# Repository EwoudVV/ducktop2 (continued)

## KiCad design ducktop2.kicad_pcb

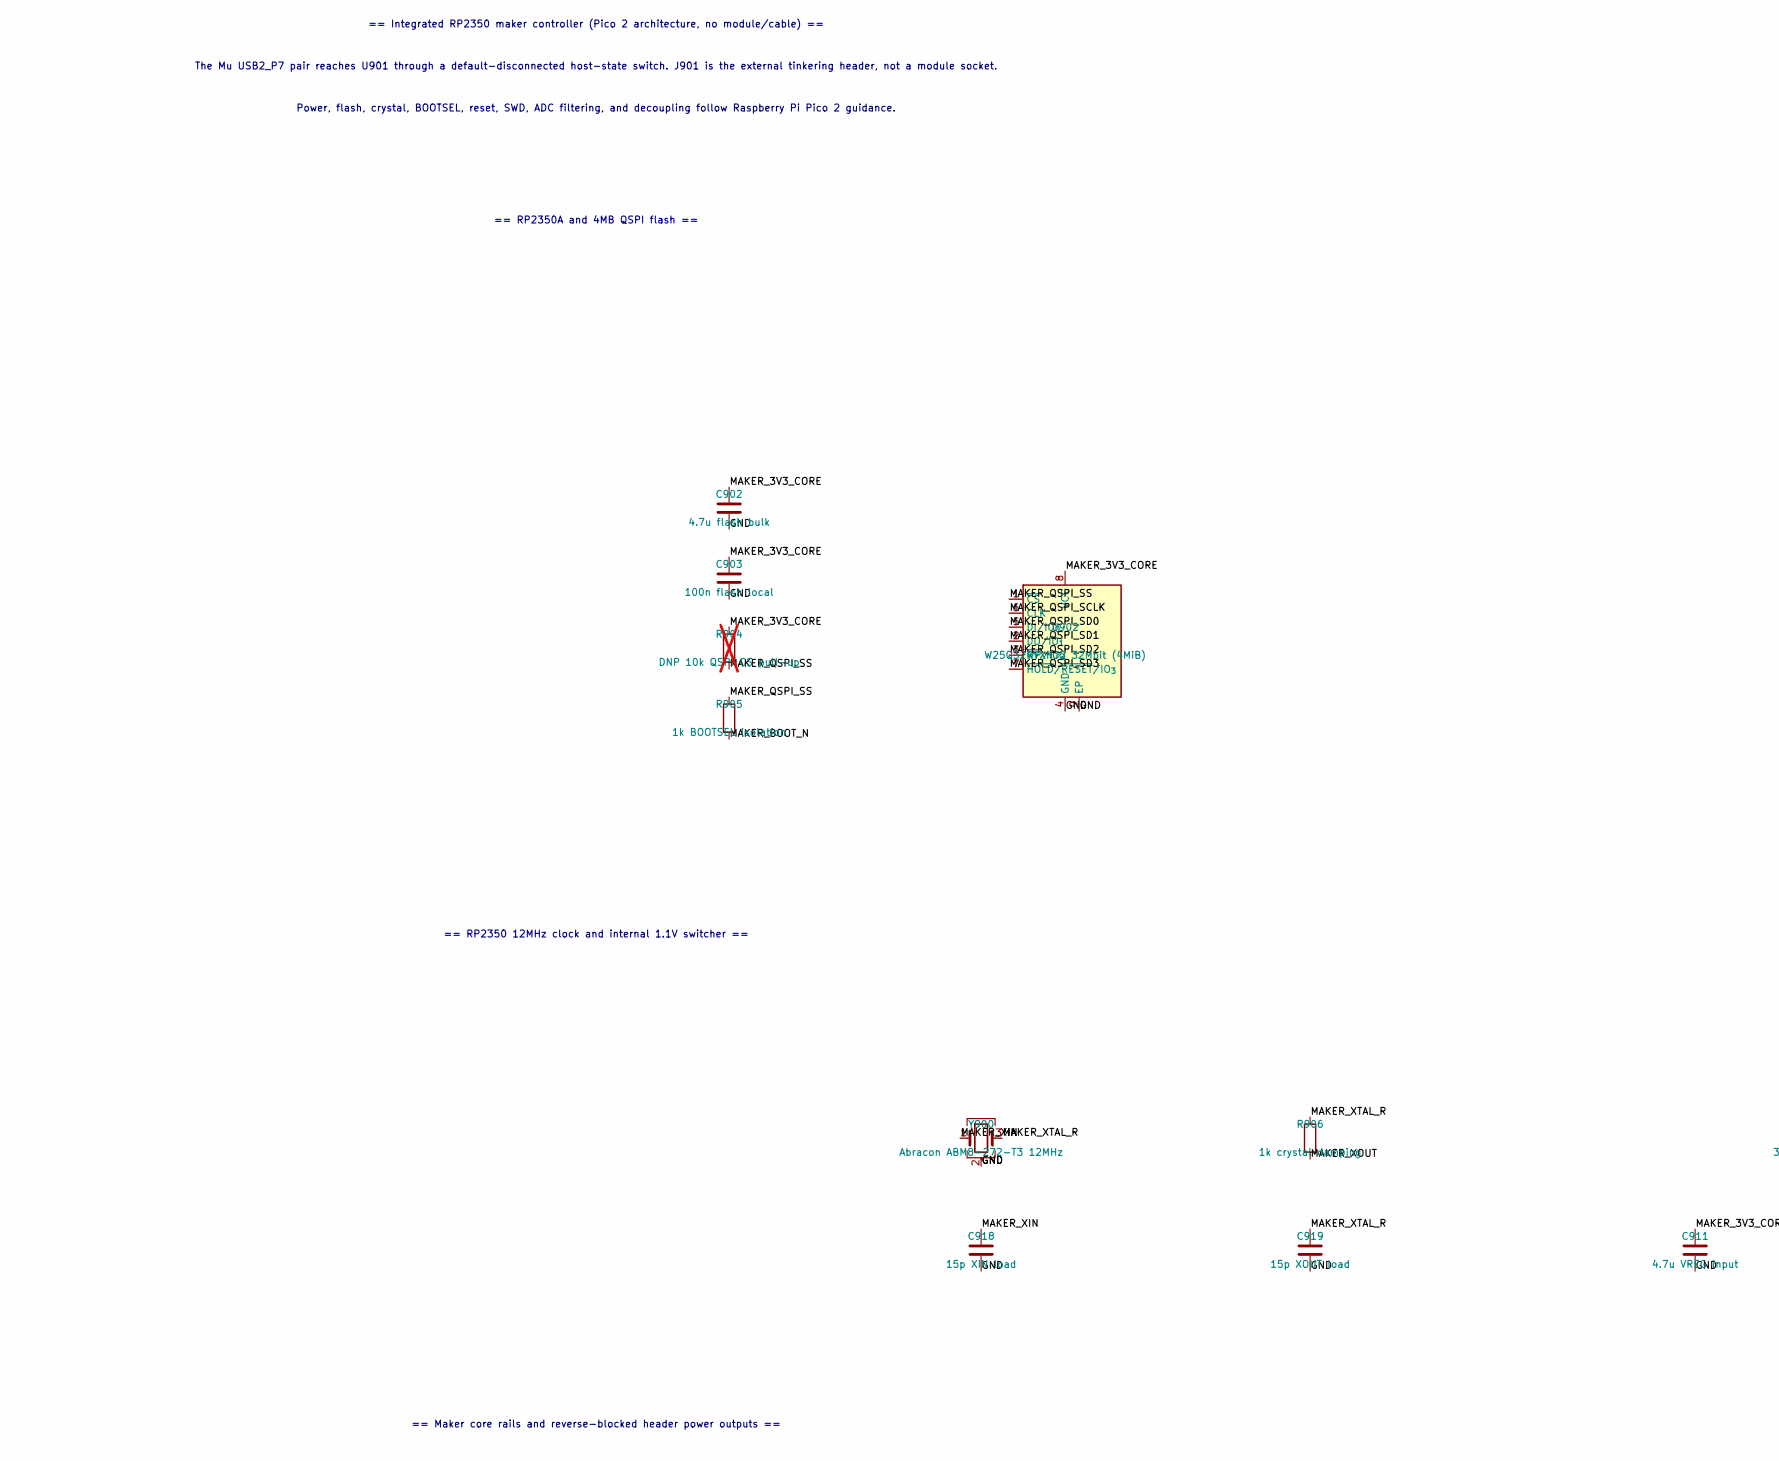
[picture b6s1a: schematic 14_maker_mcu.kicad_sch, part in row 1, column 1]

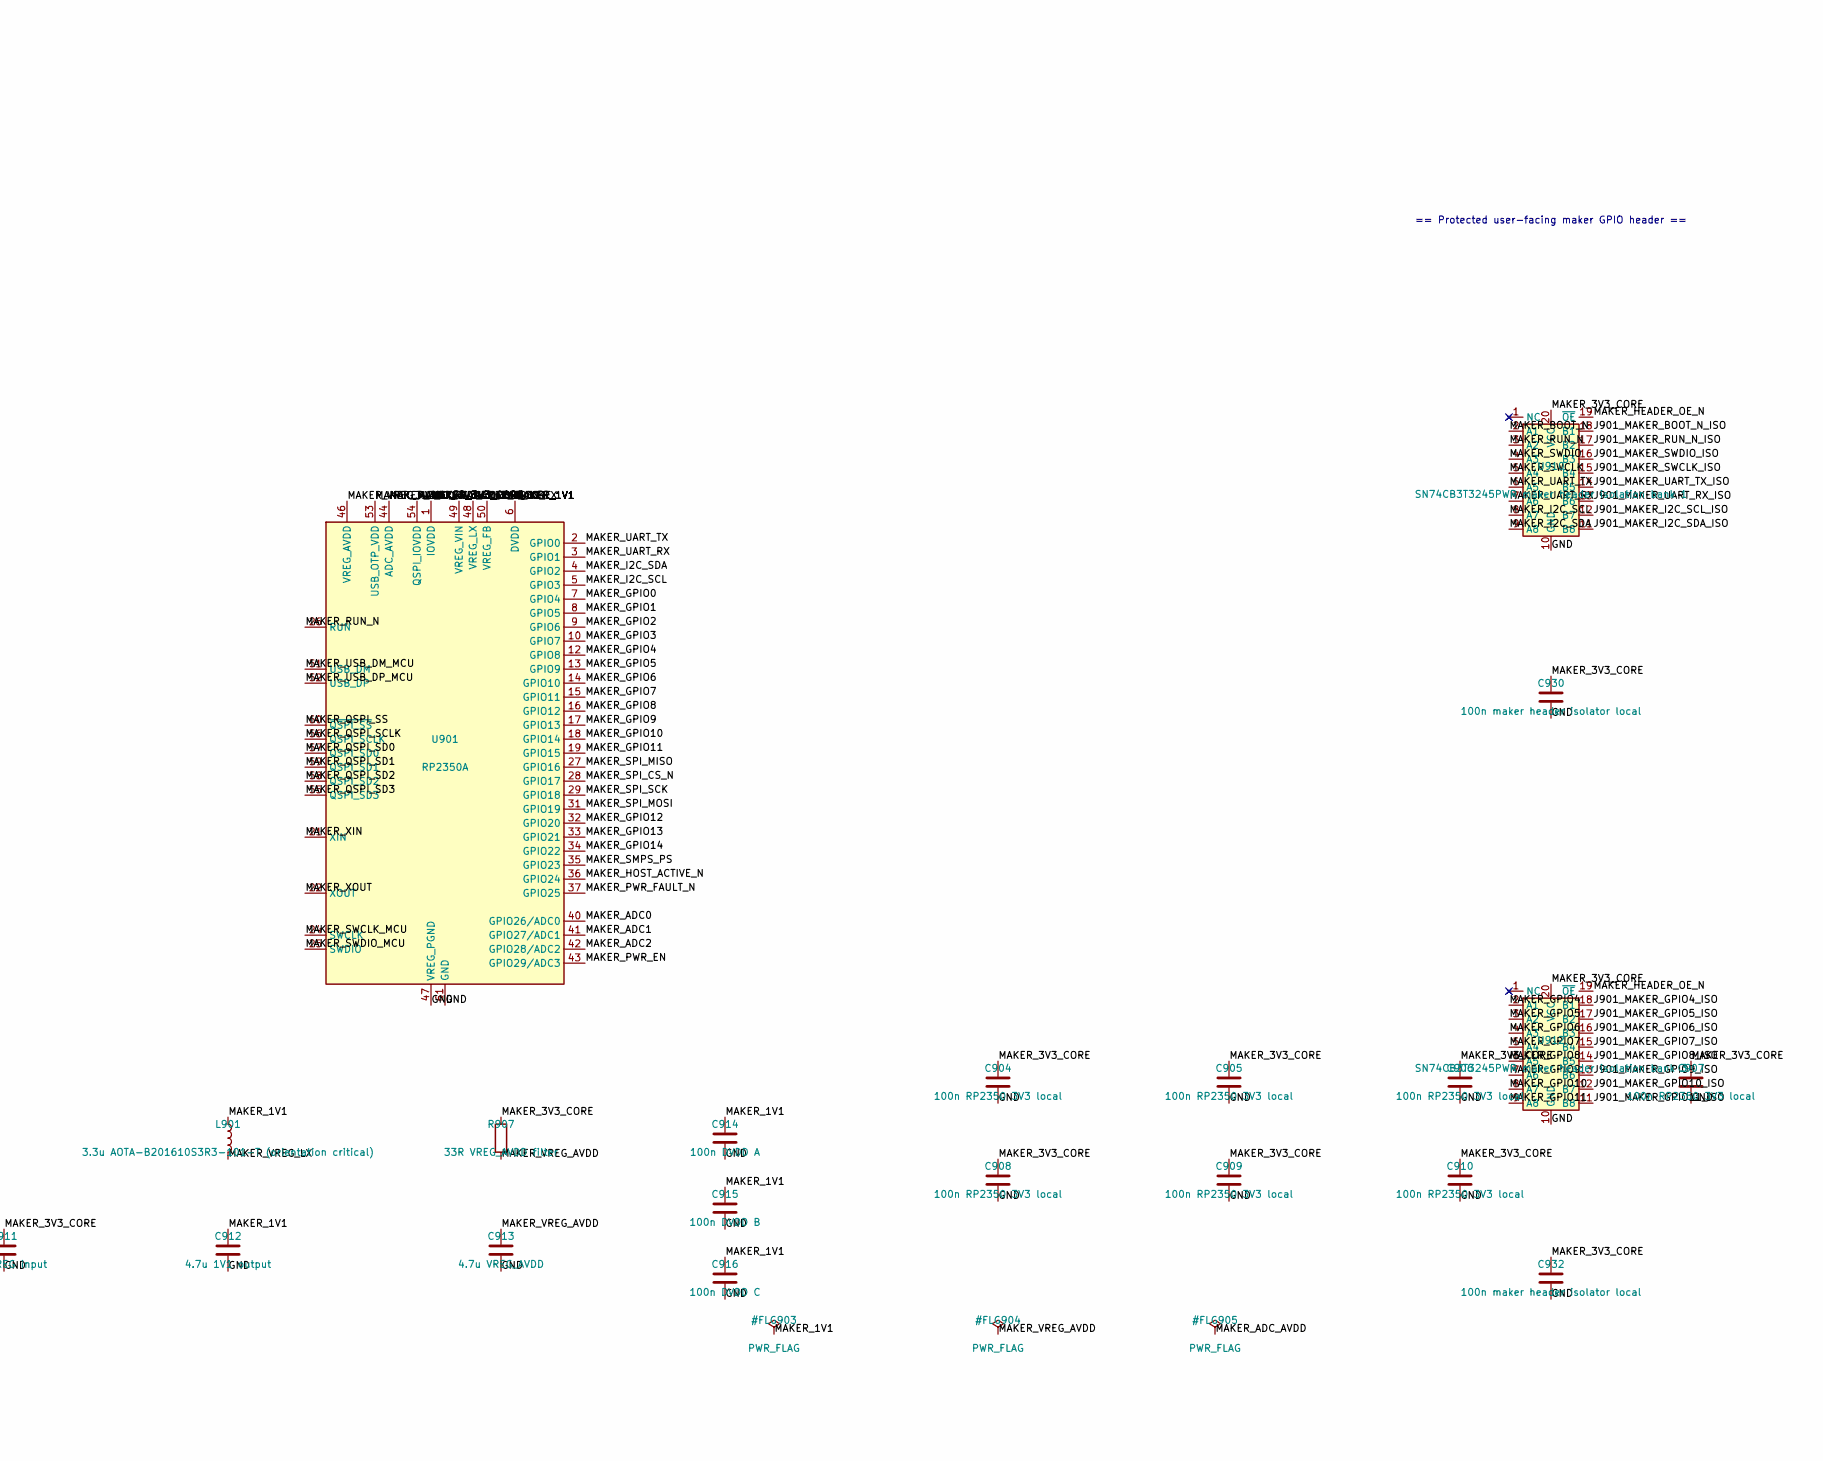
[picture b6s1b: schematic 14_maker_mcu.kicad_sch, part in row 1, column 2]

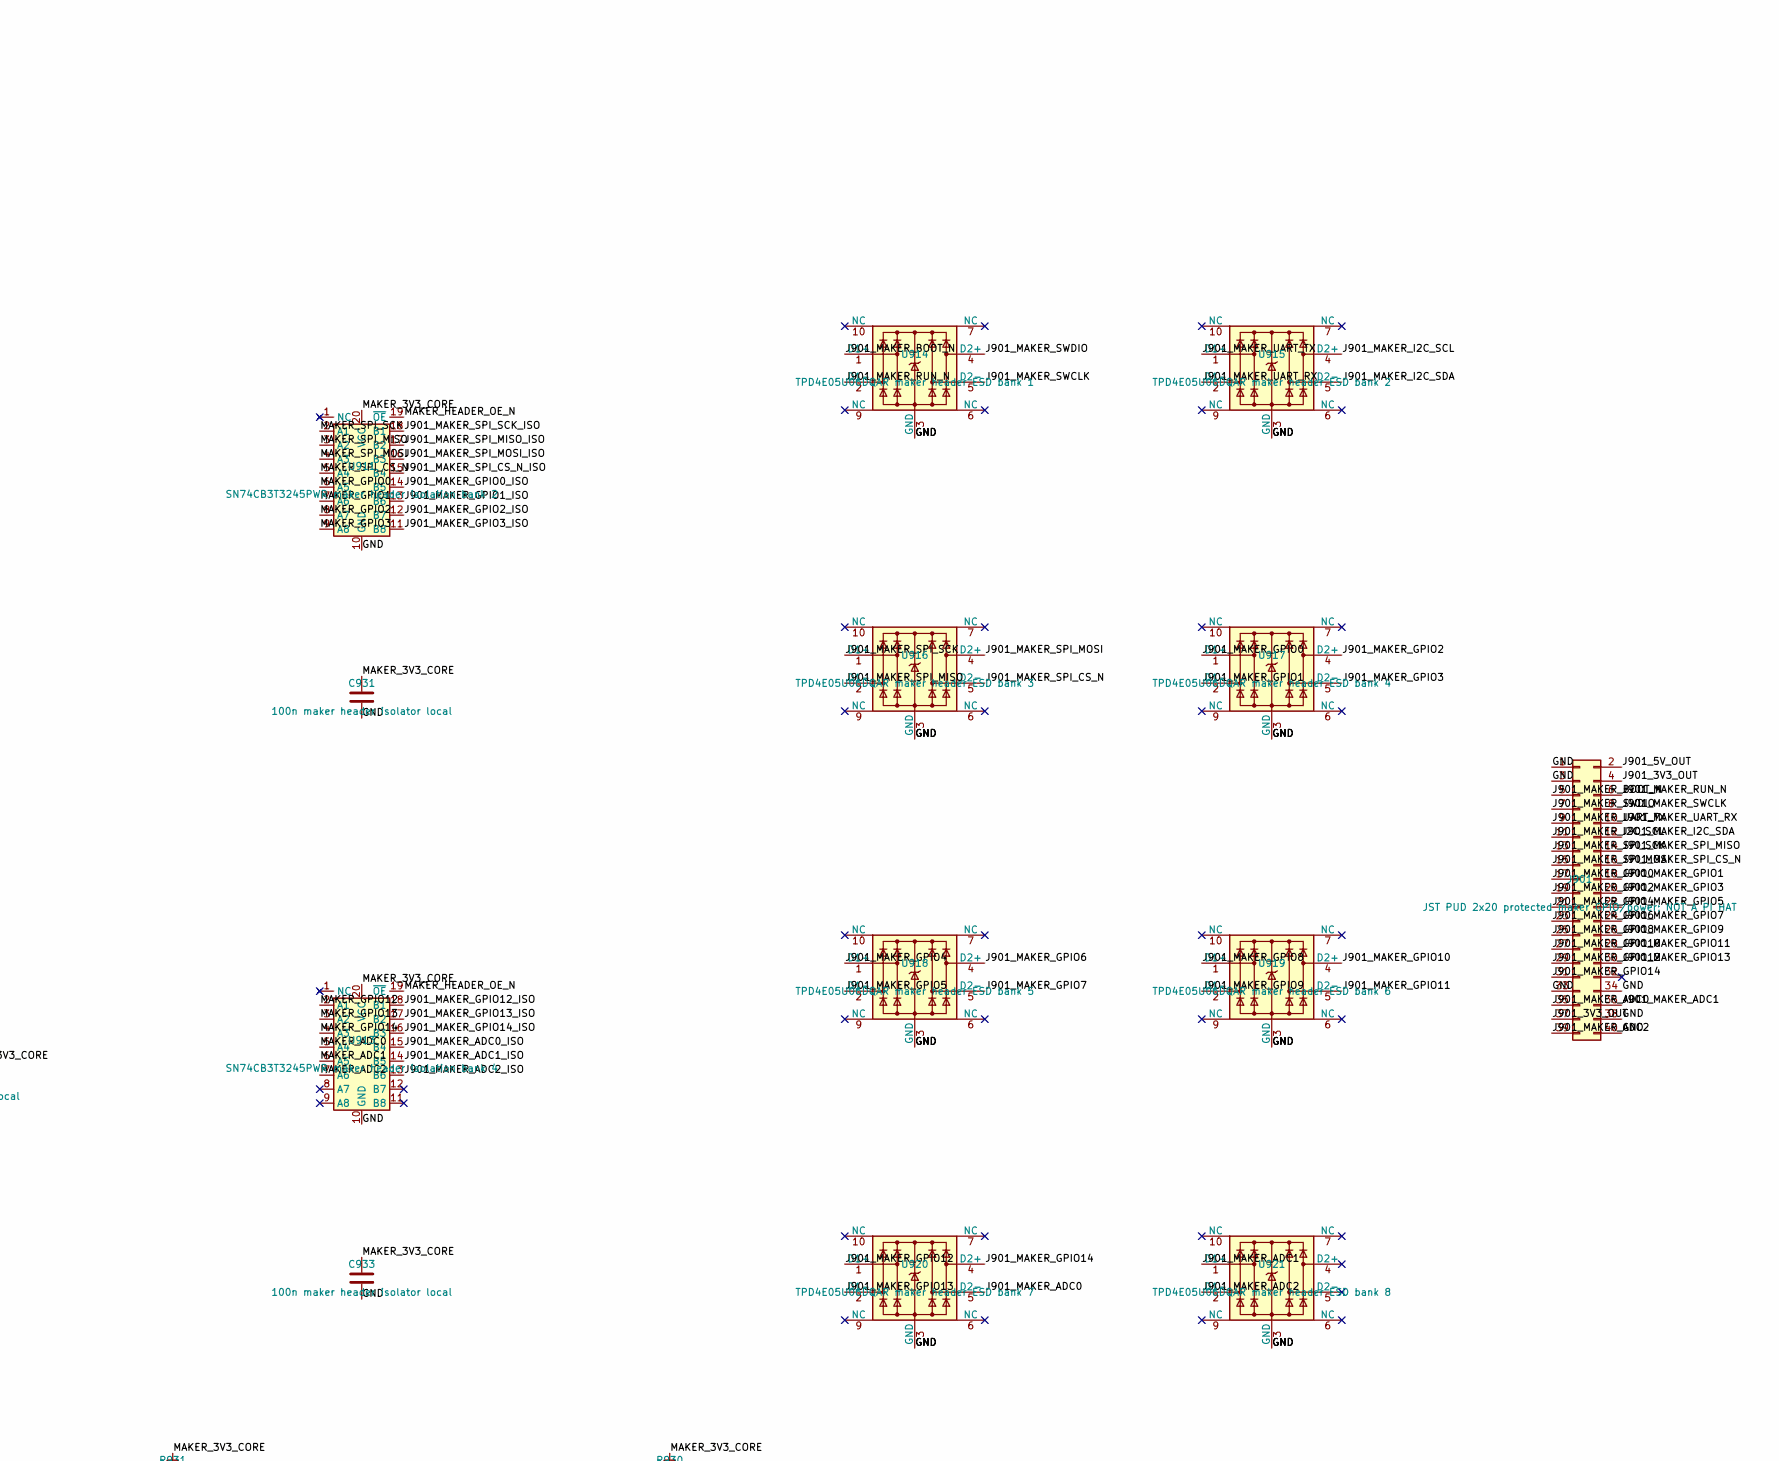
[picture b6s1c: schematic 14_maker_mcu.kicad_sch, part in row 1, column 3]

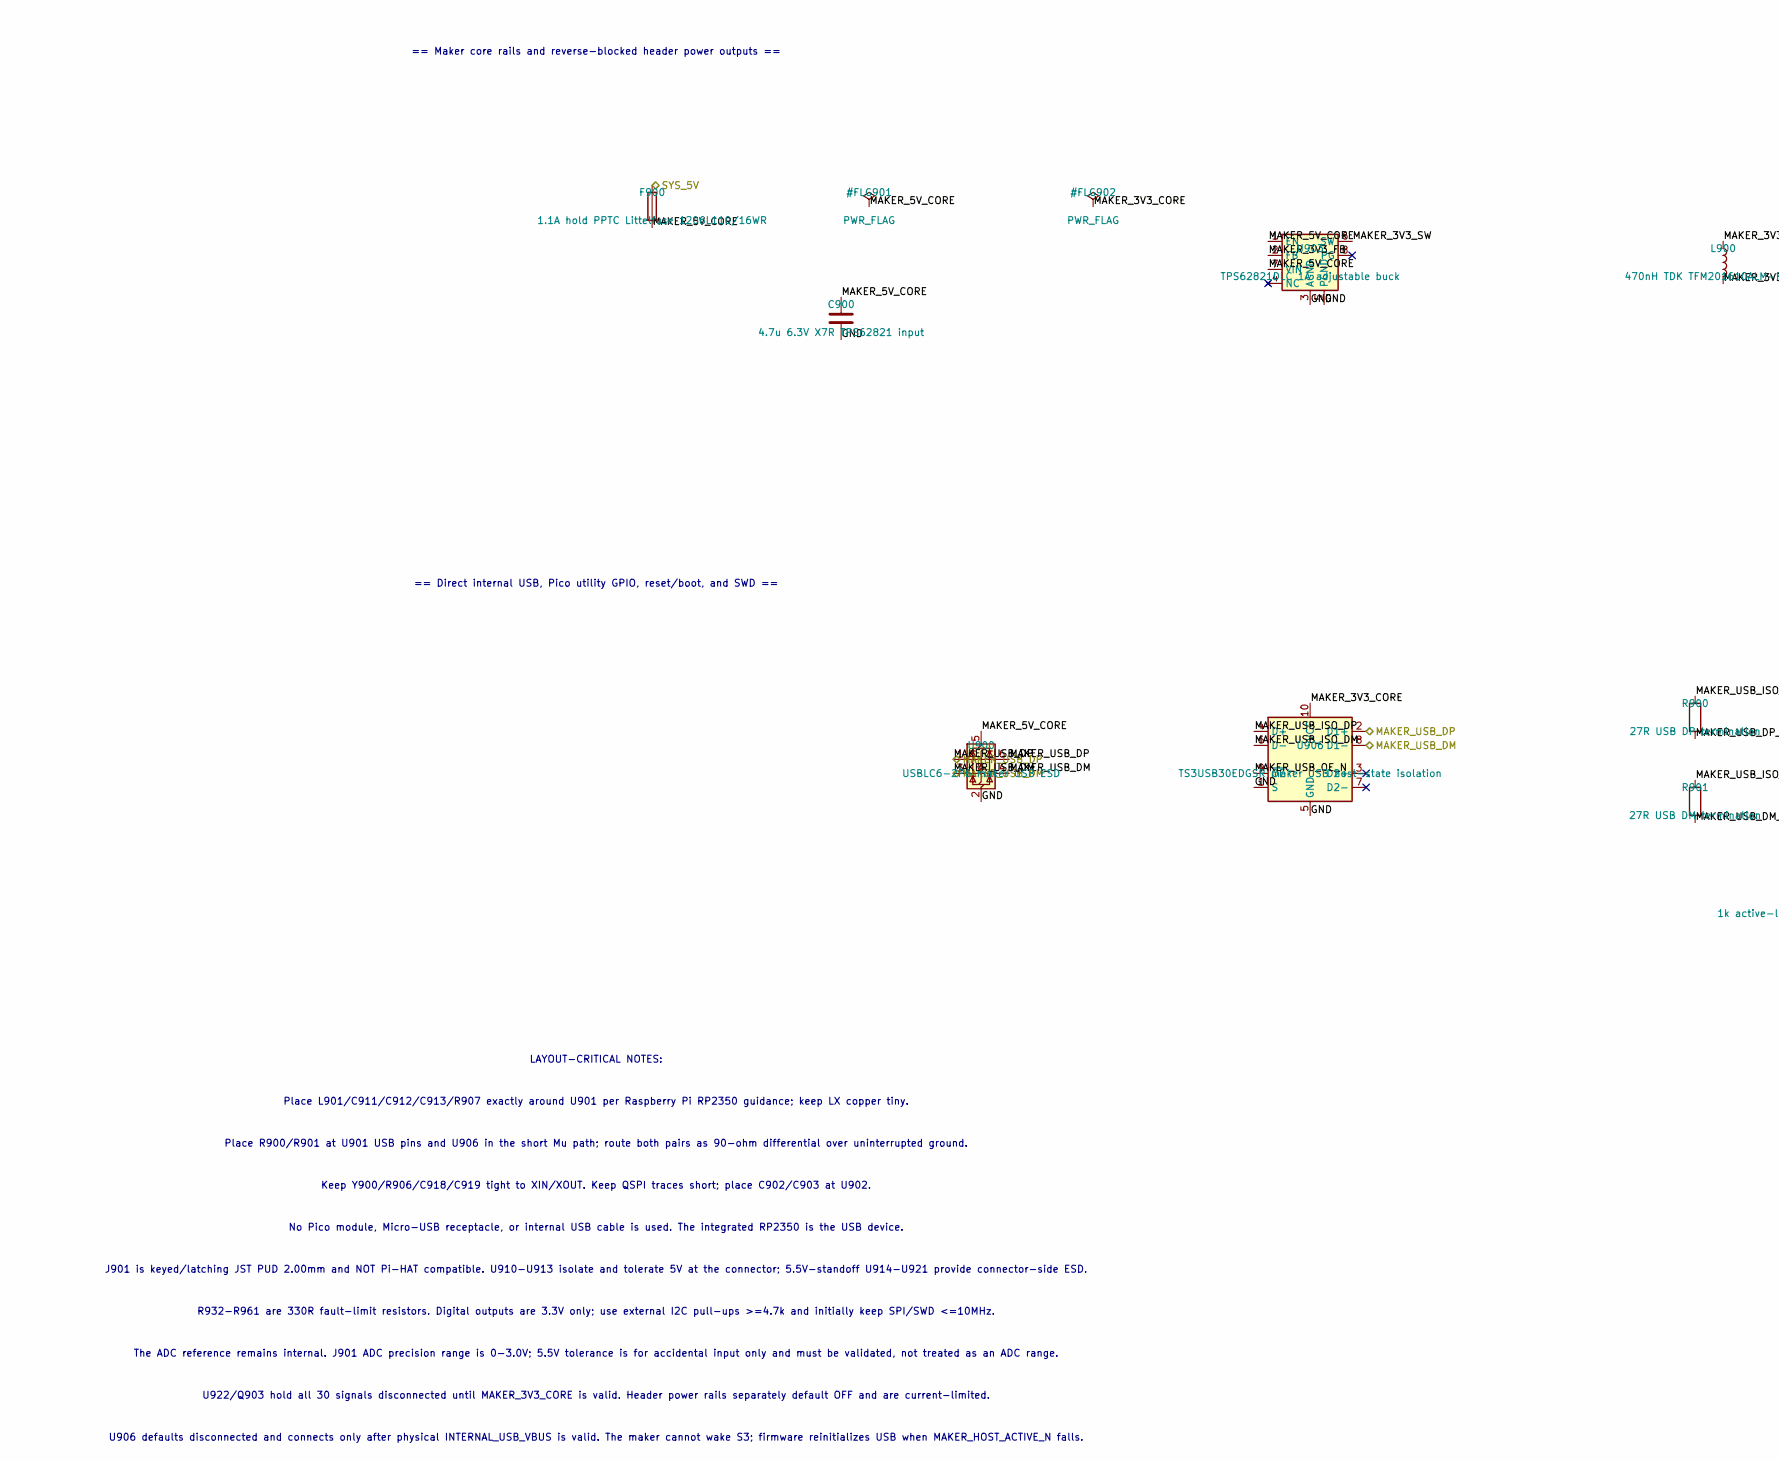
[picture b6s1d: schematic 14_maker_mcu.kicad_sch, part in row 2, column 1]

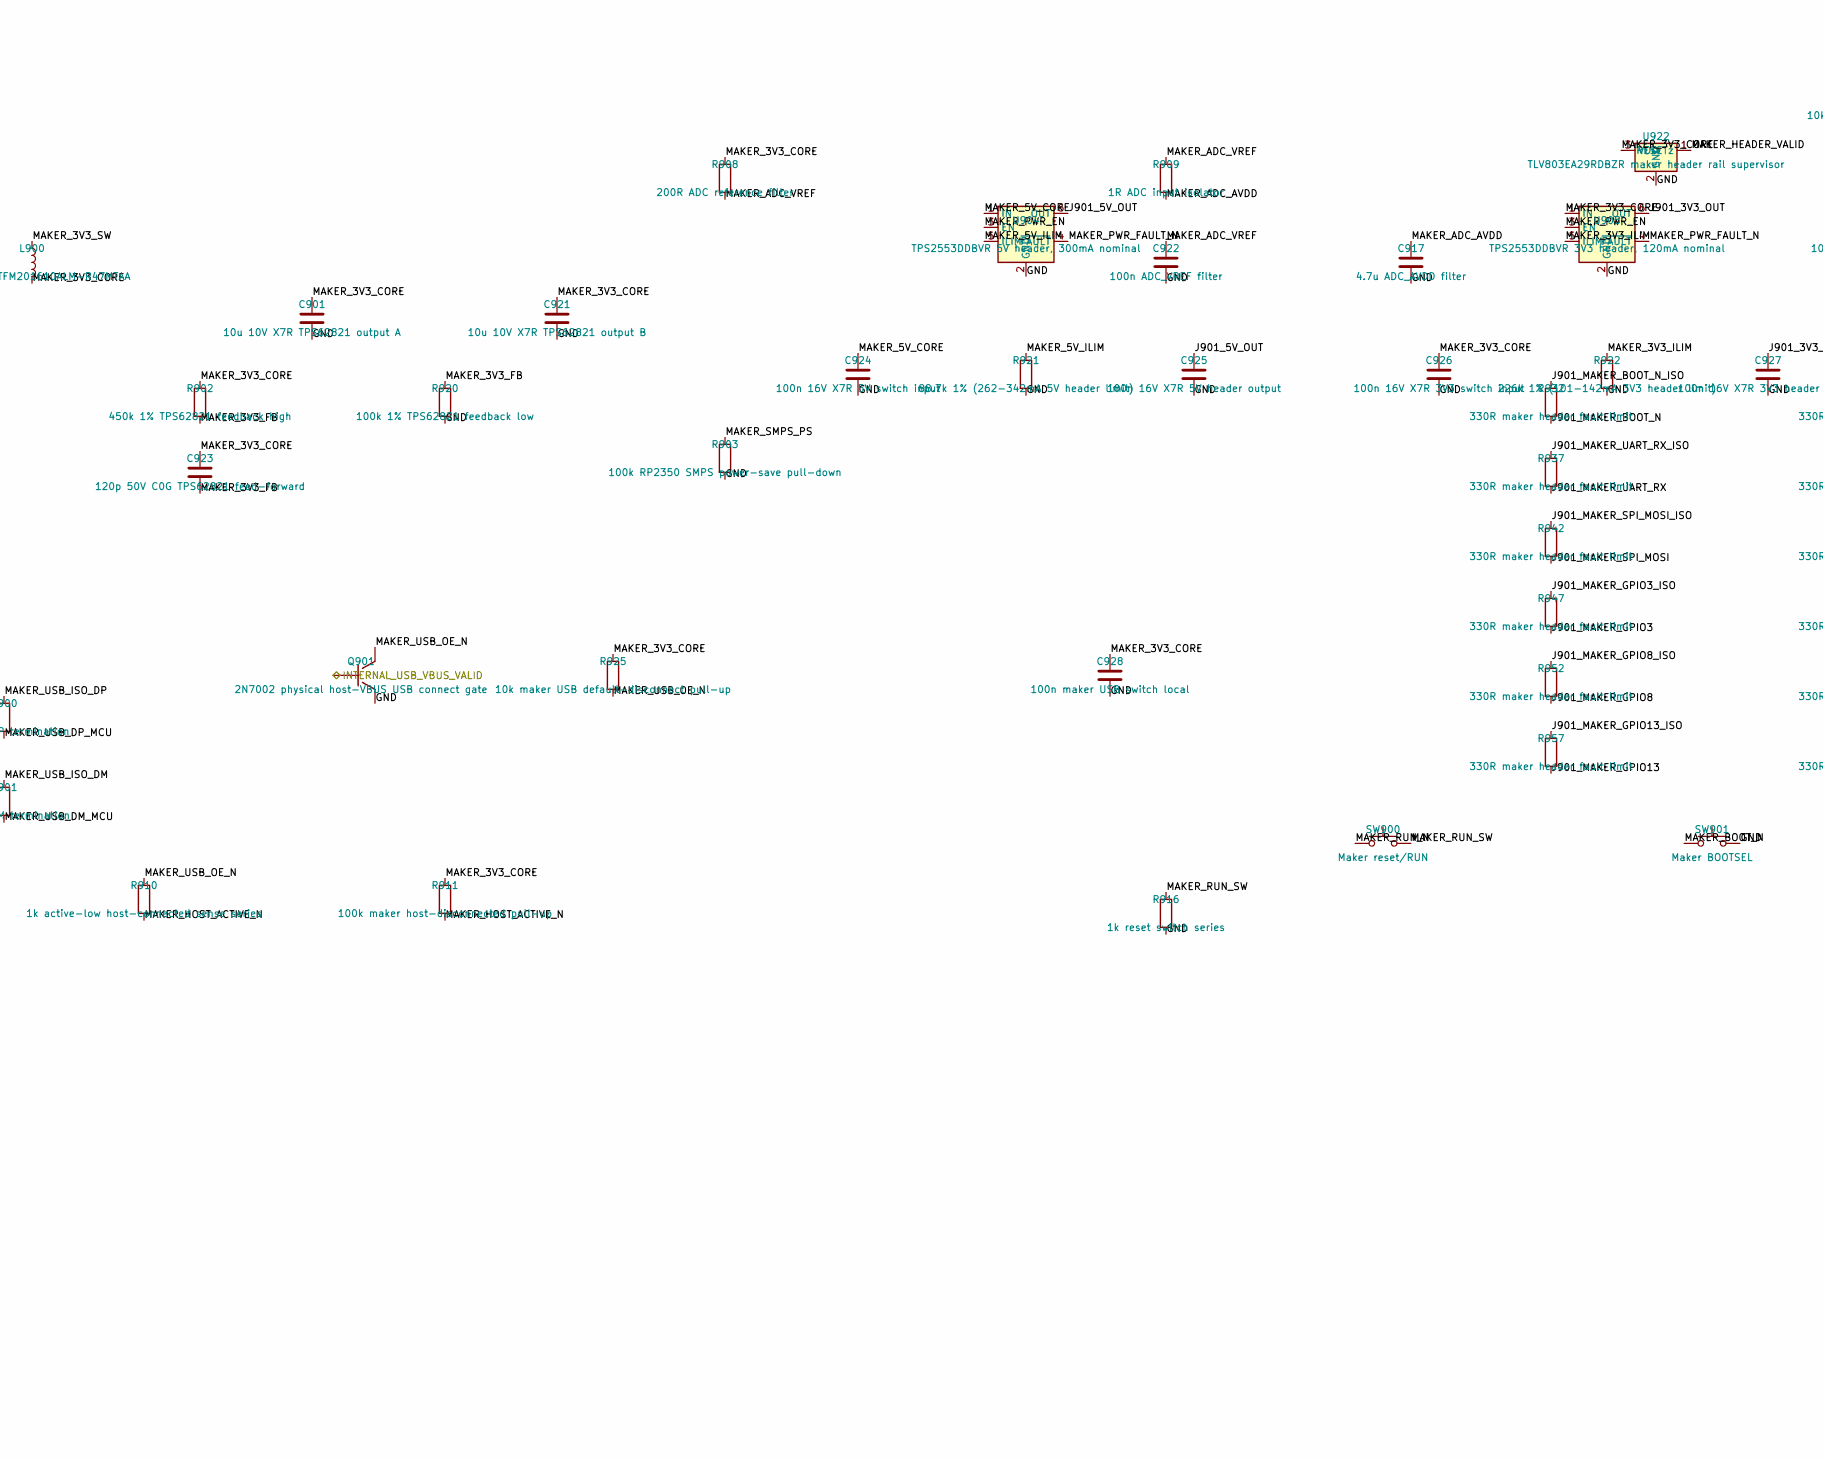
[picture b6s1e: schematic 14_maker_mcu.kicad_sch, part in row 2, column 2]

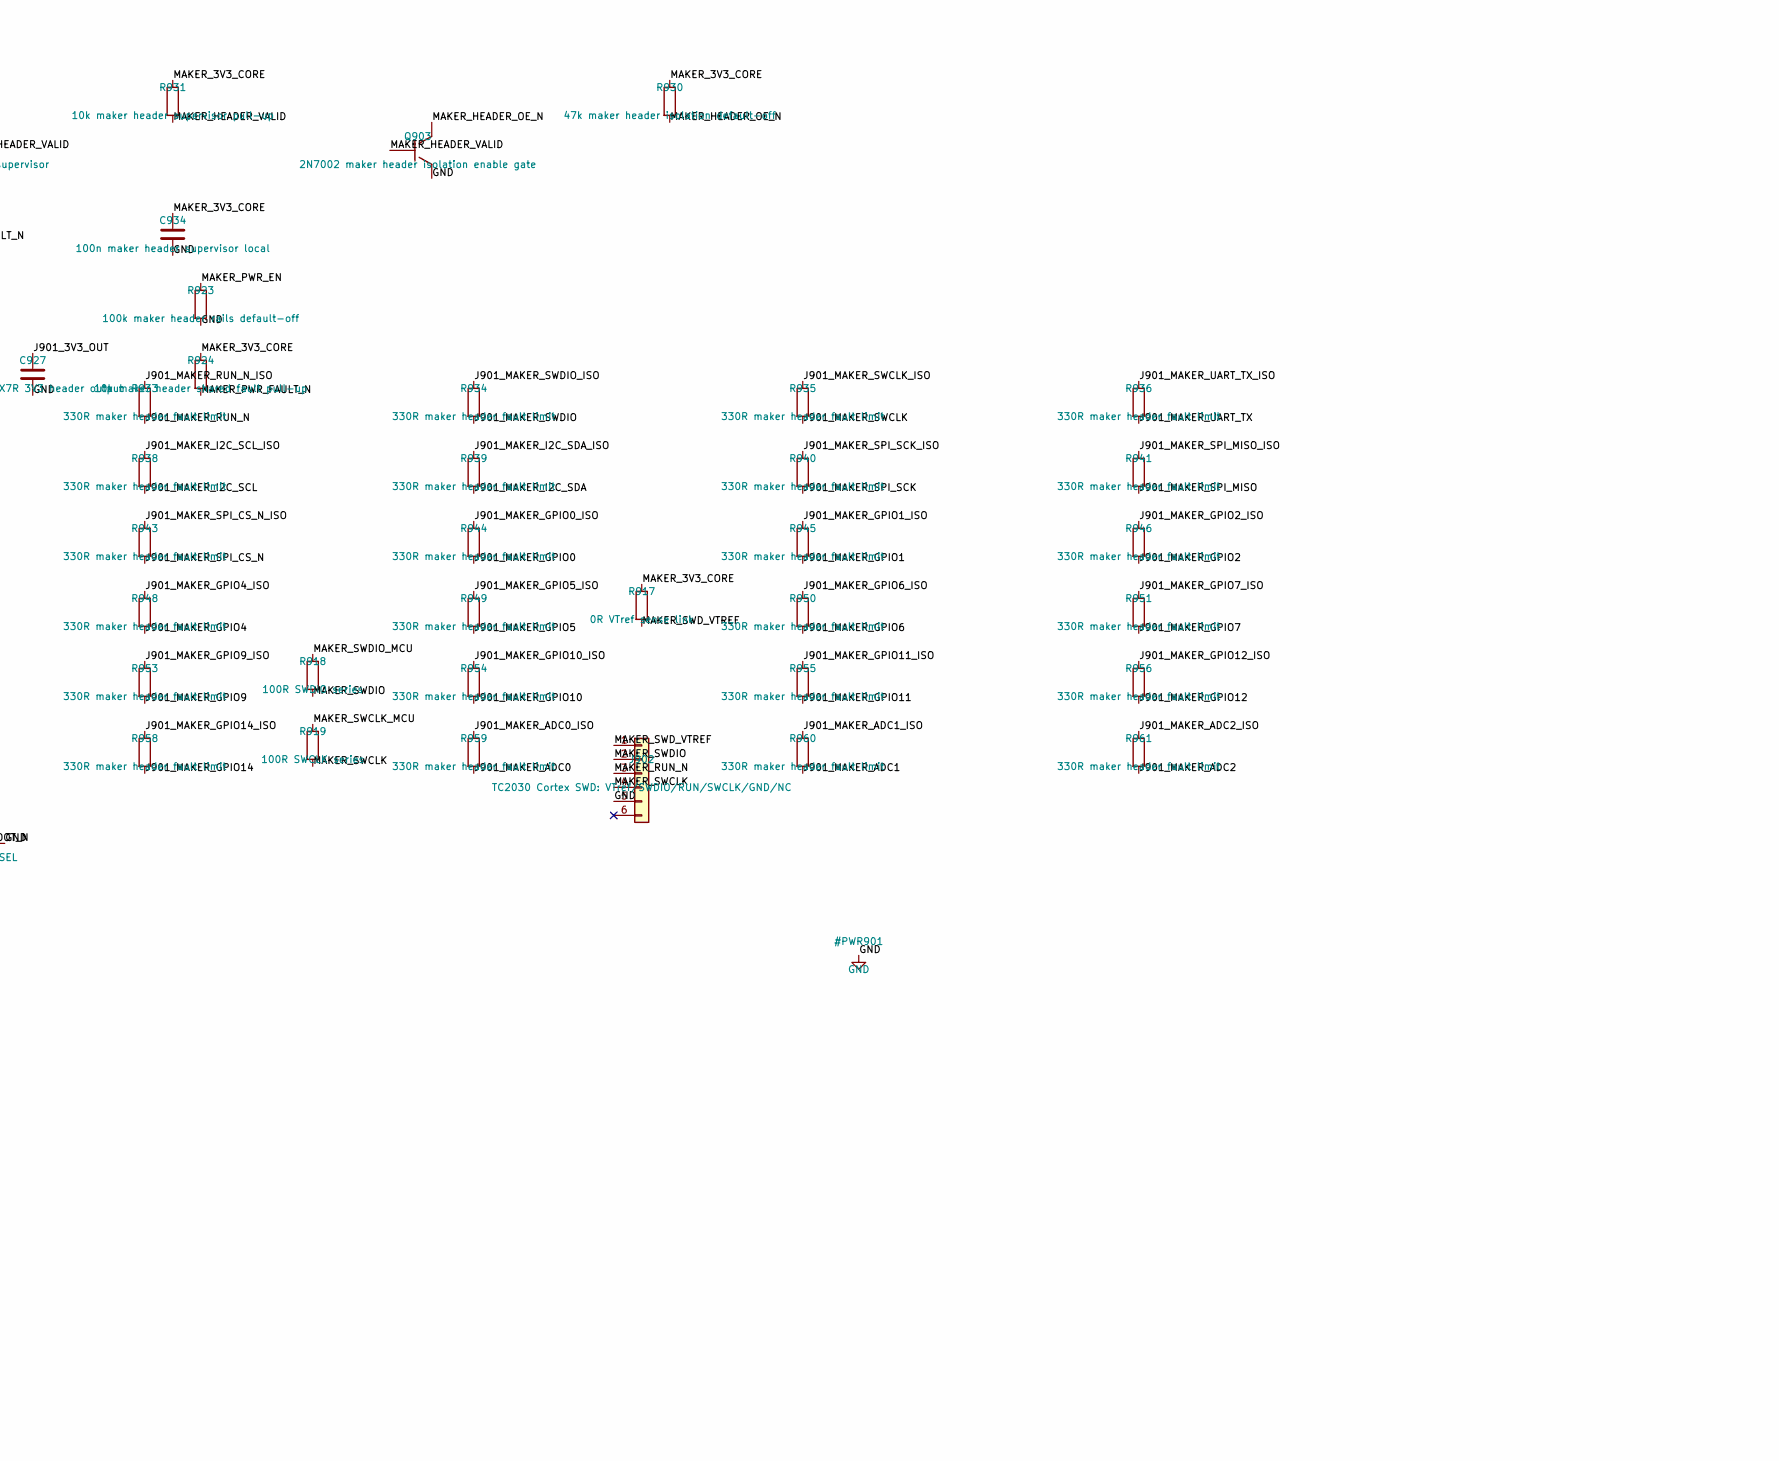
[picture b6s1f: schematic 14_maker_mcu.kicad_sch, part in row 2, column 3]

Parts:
C900: 4.7u 6.3V X7R TPS62821 input; C_0603_1608Metric; MPN JMK107BB7475MA-T
C901: 10u 10V X7R TPS62821 output A; C_0603_1608Metric; MPN GRM188Z71A106MA73D
C902: 4.7u flash bulk; C_0402_1005Metric; MPN GRM155R61A475KE15
C903: 100n flash local; C_0402_1005Metric; MPN GRM155R71A104KA01D
C904, C905, C906, C907, C908, C909, C910: 100n RP2350 3V3 local; C_0402_1005Metric; MPN GRM155R71A104KA01D
C911: 4.7u VREG input; C_0402_1005Metric; MPN GRM155R61A475KE15
C912: 4.7u 1V1 output; C_0402_1005Metric; MPN GRM155R61A475KE15
C913: 4.7u VREG_AVDD; C_0402_1005Metric; MPN GRM155R61A475KE15
C914: 100n DVDD A; C_0402_1005Metric; MPN GRM155R71A104KA01D
C915: 100n DVDD B; C_0402_1005Metric; MPN GRM155R71A104KA01D
C916: 100n DVDD C; C_0402_1005Metric; MPN GRM155R71A104KA01D
C917: 4.7u ADC_AVDD filter; C_0402_1005Metric; MPN GRM155R61A475KE15
C918: 15p XIN load; C_0402_1005Metric; MPN GRM1555C1H150JA01
C919: 15p XOUT load; C_0402_1005Metric; MPN GRM1555C1H150JA01
C921: 10u 10V X7R TPS62821 output B; C_0603_1608Metric; MPN GRM188Z71A106MA73D
C922: 100n ADC_VREF filter; C_0402_1005Metric; MPN GRM155R71A104KA01D
C923: 120p 50V C0G TPS62821 feed-forward; C_0603_1608Metric; MPN GRM1885C1H121JA01D
C924: 100n 16V X7R 5V switch input; C_0603_1608Metric; MPN C1608X7R1C104K080AA
C925: 100n 16V X7R 5V header output; C_0603_1608Metric; MPN C1608X7R1C104K080AA
C926: 100n 16V X7R 3V3 switch input; C_0603_1608Metric; MPN C1608X7R1C104K080AA
C927: 100n 16V X7R 3V3 header output; C_0603_1608Metric; MPN C1608X7R1C104K080AA
C928: 100n maker USB switch local; C_0603_1608Metric; MPN GRM188R71H104KA93D
C930, C931, C932, C933: 100n maker header isolator local; C_0603_1608Metric; MPN GRM188R71H104KA93D
C934: 100n maker header supervisor local; C_0603_1608Metric; MPN GRM188R71H104KA93D
F900: 1.1A hold PPTC Littelfuse 1206L110/16WR; Fuse_1206_3216Metric; MPN 1206L110/16WR
J901: JST PUD 2x20 protected maker GPIO/power; NOT A PI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; JST_PUD_B40B-PUDSS_2x20_P2.00mm_Vertical; MPN B40B-PUDSS
J902: TC2030 Cortex SWD: VTref/SWDIO/RUN/SWCLK/GND/NC; Tag-Connect_TC2030-IDC-NL_2x03_P1.27mm_Vertical
L900: 470nH TDK TFM201610ALM-R47MTAA; TDK_TFM201610; MPN TFM201610ALM-R47MTAA
L901: 3.3u AOTA-B201610S3R3-101-T (orientation critical); L_Wuerth_PMFI-201610_PMCI-compatible; MPN AOTA-B201610S3R3-101-T
Q901: 2N7002 physical host-VBUS USB connect gate; SOT-23; MPN 2N7002KT1G
Q903: 2N7002 maker header isolation enable gate; SOT-23; MPN 2N7002KT1G
R900: 27R USB DP termination; R_0402_1005Metric; MPN RC0402FR-0727RL
R901: 27R USB DM termination; R_0402_1005Metric; MPN RC0402FR-0727RL
R902: 450k 1% TPS62821 feedback high; R_0603_1608Metric; MPN RC0603FR-07450KL
R903: 100k RP2350 SMPS power-save pull-down; R_0402_1005Metric; MPN RC0402FR-07100KL
R904: DNP 10k QSPI CS pull-up; R_0402_1005Metric; not fitted
R905: 1k BOOTSEL isolation; R_0402_1005Metric; MPN RC0402FR-071KL
R906: 1k crystal damping; R_0402_1005Metric; MPN RC0402FR-071KL
R907: 33R VREG_AVDD filter; R_0402_1005Metric; MPN RC0402FR-0733RL
R908: 200R ADC reference filter; R_0402_1005Metric; MPN RC0402FR-07200RL
R909: 1R ADC input isolator; R_0402_1005Metric; MPN RC0402FR-071RL
R910: 1k active-low host-connected sense series; R_0402_1005Metric; MPN RC0402FR-071KL
R911: 100k maker host-disconnected pull-up; R_0402_1005Metric; MPN RC0402FR-07100KL
R916: 1k reset switch series; R_0402_1005Metric; MPN RC0402FR-071KL
R917: 0R VTref sense link; R_0402_1005Metric; MPN RC0402FR-070RL
R918: 100R SWDIO series; R_0402_1005Metric; MPN RC0402FR-07100RL
R919: 100R SWCLK series; R_0402_1005Metric; MPN RC0402FR-07100RL
R920: 100k 1% TPS62821 feedback low; R_0603_1608Metric; MPN RC0603FR-07100KL
R921: 88.7k 1% (262-342mA 5V header limit); R_0603_1608Metric; MPN RC0603FR-0788K7L
R922: 226k 1% (101-142mA 3V3 header limit); R_0603_1608Metric; MPN RC0603FR-07226KL
R923: 100k maker header rails default-off; R_0603_1608Metric; MPN RC0603FR-07100KL
R924: 10k maker header shared fault pull-up; R_0603_1608Metric; MPN RC0603FR-0710KL
R925: 10k maker USB default-disconnect pull-up; R_0402_1005Metric; MPN RC0402FR-0710KL
R930: 47k maker header isolation default-off; R_0402_1005Metric; MPN RC0402FR-0747KL
R931: 10k maker header supervisor pull-up; R_0402_1005Metric; MPN RC0402FR-0710KL
R932, R933, R934, R935, R936, R937, R938, R939, R940, R941, R942, R943, R944, R945, R946, R947, R948, R949, R950, R951, R952, R953, R954, R955, R956, R957, R958, R959, R960, R961: 330R maker header fault limit; R_0402_1005Metric; MPN RC0402FR-07330RL
SW900: Maker reset/RUN; SW_SPST_B3S-1000; MPN B3S-1000
SW901: Maker BOOTSEL; SW_SPST_B3S-1000; MPN B3S-1000
U900: USBLC6-2P6 maker USB ESD; SOT-666; MPN USBLC6-2P6
U901: RP2350A; QFN-60-1EP_7x7mm_P0.4mm_EP3.4x3.4mm_ThermalVias; MPN RP2350A (A4 stepping)
U902: W25Q32RVXHJQ 32Mbit (4MiB); Winbond_USON-8-1EP_3x2mm_P0.5mm_EP0.2x1.6mm; MPN W25Q32RVXHJQ
U903: TPS62821DLC 1A adjustable buck; Texas_VSON-HR-8_1.5x2mm_P0.5mm; MPN TPS62821DLCR
U904: TPS2553DDBVR 5V header, 300mA nominal; SOT-23-6; MPN TPS2553DDBVR
U905: TPS2553DDBVR 3V3 header, 120mA nominal; SOT-23-6; MPN TPS2553DDBVR
U906: TS3USB30EDGSR maker USB host-state isolation; TSSOP-10_3x3mm_P0.5mm; MPN TS3USB30EDGSR
U910: SN74CB3T3245PWR maker header isolation bank 1; TSSOP-20_4.4x6.5mm_P0.65mm; MPN SN74CB3T3245PWR
U911: SN74CB3T3245PWR maker header isolation bank 2; TSSOP-20_4.4x6.5mm_P0.65mm; MPN SN74CB3T3245PWR
U912: SN74CB3T3245PWR maker header isolation bank 3; TSSOP-20_4.4x6.5mm_P0.65mm; MPN SN74CB3T3245PWR
U913: SN74CB3T3245PWR maker header isolation bank 4; TSSOP-20_4.4x6.5mm_P0.65mm; MPN SN74CB3T3245PWR
U914: TPD4E05U06DQAR maker header ESD bank 1; USON-10_2.5x1.0mm_P0.5mm; MPN TPD4E05U06DQAR
U915: TPD4E05U06DQAR maker header ESD bank 2; USON-10_2.5x1.0mm_P0.5mm; MPN TPD4E05U06DQAR
U916: TPD4E05U06DQAR maker header ESD bank 3; USON-10_2.5x1.0mm_P0.5mm; MPN TPD4E05U06DQAR
U917: TPD4E05U06DQAR maker header ESD bank 4; USON-10_2.5x1.0mm_P0.5mm; MPN TPD4E05U06DQAR
U918: TPD4E05U06DQAR maker header ESD bank 5; USON-10_2.5x1.0mm_P0.5mm; MPN TPD4E05U06DQAR
U919: TPD4E05U06DQAR maker header ESD bank 6; USON-10_2.5x1.0mm_P0.5mm; MPN TPD4E05U06DQAR
U920: TPD4E05U06DQAR maker header ESD bank 7; USON-10_2.5x1.0mm_P0.5mm; MPN TPD4E05U06DQAR
U921: TPD4E05U06DQAR maker header ESD bank 8; USON-10_2.5x1.0mm_P0.5mm; MPN TPD4E05U06DQAR
U922: TLV803EA29RDBZR maker header rail supervisor; SOT-23-3; MPN TLV803EA29RDBZR
Y900: Abracon ABM8-272-T3 12MHz; Crystal_SMD_3225-4Pin_3.2x2.5mm; MPN ABM8-272-T3

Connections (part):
/INTERNAL_USB_VBUS_VALID: Q901.1 (G); also elsewhere on the board
/MAKER_USB_DM: U900.3 (I/O2), U900.4 (I/O2), U906.8 (D1-); also elsewhere on the board
/MAKER_USB_DP: U900.1 (I/O1), U900.6 (I/O1), U906.2 (D1+); also elsewhere on the board
/Maker MCU/J901_3V3_OUT: C927.1, J901.4, J901.37, U905.6 (OUT)
/Maker MCU/J901_5V_OUT: C925.1, J901.2, U904.6 (OUT)
/Maker MCU/J901_MAKER_ADC0: J901.35, R959.2, U920.5 (D2-)
/Maker MCU/J901_MAKER_ADC0_ISO: R959.1, U913.15 (B4)
/Maker MCU/J901_MAKER_ADC1: J901.36, R960.2, U921.1 (D1+)
/Maker MCU/J901_MAKER_ADC1_ISO: R960.1, U913.14 (B5)
/Maker MCU/J901_MAKER_ADC2: J901.39, R961.2, U921.2 (D1-)
/Maker MCU/J901_MAKER_ADC2_ISO: R961.1, U913.13 (B6)
/Maker MCU/J901_MAKER_BOOT_N: J901.5, R932.2, U914.1 (D1+)
/Maker MCU/J901_MAKER_BOOT_N_ISO: R932.1, U910.18 (B1)
/Maker MCU/J901_MAKER_GPIO0: J901.17, R944.2, U917.1 (D1+)
/Maker MCU/J901_MAKER_GPIO0_ISO: R944.1, U911.14 (B5)
/Maker MCU/J901_MAKER_GPIO1: J901.18, R945.2, U917.2 (D1-)
/Maker MCU/J901_MAKER_GPIO1_ISO: R945.1, U911.13 (B6)
/Maker MCU/J901_MAKER_GPIO2: J901.19, R946.2, U917.4 (D2+)
/Maker MCU/J901_MAKER_GPIO2_ISO: R946.1, U911.12 (B7)
/Maker MCU/J901_MAKER_GPIO3: J901.20, R947.2, U917.5 (D2-)
/Maker MCU/J901_MAKER_GPIO3_ISO: R947.1, U911.11 (B8)
/Maker MCU/J901_MAKER_GPIO4: J901.21, R948.2, U918.1 (D1+)
/Maker MCU/J901_MAKER_GPIO4_ISO: R948.1, U912.18 (B1)
/Maker MCU/J901_MAKER_GPIO5: J901.22, R949.2, U918.2 (D1-)
/Maker MCU/J901_MAKER_GPIO5_ISO: R949.1, U912.17 (B2)
/Maker MCU/J901_MAKER_GPIO6: J901.23, R950.2, U918.4 (D2+)
/Maker MCU/J901_MAKER_GPIO6_ISO: R950.1, U912.16 (B3)
/Maker MCU/J901_MAKER_GPIO7: J901.24, R951.2, U918.5 (D2-)
/Maker MCU/J901_MAKER_GPIO7_ISO: R951.1, U912.15 (B4)
/Maker MCU/J901_MAKER_GPIO8: J901.25, R952.2, U919.1 (D1+)
/Maker MCU/J901_MAKER_GPIO8_ISO: R952.1, U912.14 (B5)
/Maker MCU/J901_MAKER_GPIO9: J901.26, R953.2, U919.2 (D1-)
/Maker MCU/J901_MAKER_GPIO9_ISO: R953.1, U912.13 (B6)
/Maker MCU/J901_MAKER_GPIO10: J901.27, R954.2, U919.4 (D2+)
/Maker MCU/J901_MAKER_GPIO10_ISO: R954.1, U912.12 (B7)
/Maker MCU/J901_MAKER_GPIO11: J901.28, R955.2, U919.5 (D2-)
/Maker MCU/J901_MAKER_GPIO11_ISO: R955.1, U912.11 (B8)
/Maker MCU/J901_MAKER_GPIO12: J901.29, R956.2, U920.1 (D1+)
/Maker MCU/J901_MAKER_GPIO12_ISO: R956.1, U913.18 (B1)
/Maker MCU/J901_MAKER_GPIO13: J901.30, R957.2, U920.2 (D1-)
/Maker MCU/J901_MAKER_GPIO13_ISO: R957.1, U913.17 (B2)
/Maker MCU/J901_MAKER_GPIO14: J901.31, R958.2, U920.4 (D2+)
/Maker MCU/J901_MAKER_GPIO14_ISO: R958.1, U913.16 (B3)
/Maker MCU/J901_MAKER_I2C_SCL: J901.11, R938.2, U915.4 (D2+)
/Maker MCU/J901_MAKER_I2C_SCL_ISO: R938.1, U910.12 (B7)
/Maker MCU/J901_MAKER_I2C_SDA: J901.12, R939.2, U915.5 (D2-)
/Maker MCU/J901_MAKER_I2C_SDA_ISO: R939.1, U910.11 (B8)
/Maker MCU/J901_MAKER_RUN_N: J901.6, R933.2, U914.2 (D1-)
/Maker MCU/J901_MAKER_RUN_N_ISO: R933.1, U910.17 (B2)
/Maker MCU/J901_MAKER_SPI_CS_N: J901.16, R943.2, U916.5 (D2-)
/Maker MCU/J901_MAKER_SPI_CS_N_ISO: R943.1, U911.15 (B4)
/Maker MCU/J901_MAKER_SPI_MISO: J901.14, R941.2, U916.2 (D1-)
/Maker MCU/J901_MAKER_SPI_MISO_ISO: R941.1, U911.17 (B2)
/Maker MCU/J901_MAKER_SPI_MOSI: J901.15, R942.2, U916.4 (D2+)
/Maker MCU/J901_MAKER_SPI_MOSI_ISO: R942.1, U911.16 (B3)
/Maker MCU/J901_MAKER_SPI_SCK: J901.13, R940.2, U916.1 (D1+)
/Maker MCU/J901_MAKER_SPI_SCK_ISO: R940.1, U911.18 (B1)
/Maker MCU/J901_MAKER_SWCLK: J901.8, R935.2, U914.5 (D2-)
/Maker MCU/J901_MAKER_SWCLK_ISO: R935.1, U910.15 (B4)
/Maker MCU/J901_MAKER_SWDIO: J901.7, R934.2, U914.4 (D2+)
/Maker MCU/J901_MAKER_SWDIO_ISO: R934.1, U910.16 (B3)
/Maker MCU/J901_MAKER_UART_RX: J901.10, R937.2, U915.2 (D1-)
/Maker MCU/J901_MAKER_UART_RX_ISO: R937.1, U910.13 (B6)
/Maker MCU/J901_MAKER_UART_TX: J901.9, R936.2, U915.1 (D1+)
/Maker MCU/J901_MAKER_UART_TX_ISO: R936.1, U910.14 (B5)
/Maker MCU/MAKER_1V1: C912.1, C914.1, C915.1, C916.1, L901.1, U901.6 (DVDD), U901.23 (DVDD), U901.39 (DVDD), U901.50 (VREG_FB)
/Maker MCU/MAKER_3V3_CORE: C901.1, C902.1, C903.1, C904.1, C905.1, C906.1, C907.1, C908.1, C909.1, C910.1, C911.1, C921.1, C923.1, C926.1, C928.1, C930.1, C931.1, C932.1, C933.1, C934.1, L900.2, R902.1, R904.1, R907.1, R908.1, R911.1, R917.1, R924.1, R925.1, R930.1, R931.1, U901.1 (IOVDD), U901.11 (IOVDD), U901.20 (IOVDD), U901.30 (IOVDD), U901.38 (IOVDD), U901.45 (IOVDD), U901.49 (VREG_VIN), U901.53 (USB_OTP_VDD), U901.54 (QSPI_IOVDD), U902.8 (VCC), U905.1 (IN), U906.10 (VCC), U910.20 (VCC), U911.20 (VCC), U912.20 (VCC), U913.20 (VCC), U922.3 (VDD)
/Maker MCU/MAKER_3V3_FB: C923.2, R902.2, R920.1, U903.2 (FB)
/Maker MCU/MAKER_3V3_ILIM: R922.1, U905.5 (ILIM)
/Maker MCU/MAKER_3V3_SW: L900.1, U903.6 (SW)
/Maker MCU/MAKER_5V_CORE: C900.1, C924.1, F900.2, U900.5 (VBUS), U903.1 (EN), U903.7 (VIN), U904.1 (IN)
/Maker MCU/MAKER_5V_ILIM: R921.1, U904.5 (ILIM)
/Maker MCU/MAKER_ADC0: U901.40 (GPIO26/ADC0), U913.5 (A4)
/Maker MCU/MAKER_ADC1: U901.41 (GPIO27/ADC1), U913.6 (A5)
/Maker MCU/MAKER_ADC2: U901.42 (GPIO28/ADC2), U913.7 (A6)
/Maker MCU/MAKER_ADC_AVDD: C917.1, R909.2, U901.44 (ADC_AVDD)
/Maker MCU/MAKER_ADC_VREF: C922.1, R908.2, R909.1
/Maker MCU/MAKER_BOOT_N: R905.2, SW901.1, U910.2 (A1)
/Maker MCU/MAKER_GPIO0: U901.7 (GPIO4), U911.6 (A5)
/Maker MCU/MAKER_GPIO1: U901.8 (GPIO5), U911.7 (A6)
/Maker MCU/MAKER_GPIO2: U901.9 (GPIO6), U911.8 (A7)
/Maker MCU/MAKER_GPIO3: U901.10 (GPIO7), U911.9 (A8)
/Maker MCU/MAKER_GPIO4: U901.12 (GPIO8), U912.2 (A1)
/Maker MCU/MAKER_GPIO5: U901.13 (GPIO9), U912.3 (A2)
/Maker MCU/MAKER_GPIO6: U901.14 (GPIO10), U912.4 (A3)
/Maker MCU/MAKER_GPIO7: U901.15 (GPIO11), U912.5 (A4)
/Maker MCU/MAKER_GPIO8: U901.16 (GPIO12), U912.6 (A5)
/Maker MCU/MAKER_GPIO9: U901.17 (GPIO13), U912.7 (A6)
/Maker MCU/MAKER_GPIO10: U901.18 (GPIO14), U912.8 (A7)
/Maker MCU/MAKER_GPIO11: U901.19 (GPIO15), U912.9 (A8)
/Maker MCU/MAKER_GPIO12: U901.32 (GPIO20), U913.2 (A1)
/Maker MCU/MAKER_GPIO13: U901.33 (GPIO21), U913.3 (A2)
/Maker MCU/MAKER_GPIO14: U901.34 (GPIO22), U913.4 (A3)
/Maker MCU/MAKER_HEADER_OE_N: Q903.3 (D), R930.2, U910.19 (~OE), U911.19 (~OE), U912.19 (~OE), U913.19 (~OE)
/Maker MCU/MAKER_HEADER_VALID: Q903.1 (G), R931.2, U922.1 (RESETz)
/Maker MCU/MAKER_HOST_ACTIVE_N: R910.2, R911.2, U901.36 (GPIO24)
/Maker MCU/MAKER_I2C_SCL: U901.5 (GPIO3), U910.8 (A7)
/Maker MCU/MAKER_I2C_SDA: U901.4 (GPIO2), U910.9 (A8)
/Maker MCU/MAKER_PWR_EN: R923.1, U901.43 (GPIO29/ADC3), U904.3 (EN), U905.3 (EN)
/Maker MCU/MAKER_PWR_FAULT_N: R924.2, U901.37 (GPIO25), U904.4 (~FAULT), U905.4 (~FAULT)
/Maker MCU/MAKER_QSPI_SCLK: U901.56 (QSPI_SCLK), U902.6 (CLK)
/Maker MCU/MAKER_QSPI_SD0: U901.57 (QSPI_SD0), U902.5 (DI/IO_{0})
/Maker MCU/MAKER_QSPI_SD1: U901.59 (QSPI_SD1), U902.2 (DO/IO_{1})
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
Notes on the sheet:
== Integrated RP2350 maker controller (Pico 2 architecture, no module/cable) ==
The Mu USB2_P7 pair reaches U901 through a default-disconnected host-state switch. J901 is the external tinkering header, not a module socket.
Power, flash, crystal, BOOTSEL, reset, SWD, ADC filtering, and decoupling follow Raspberry Pi Pico 2 guidance.
== RP2350A and 4MB QSPI flash ==
== RP2350 12MHz clock and internal 1.1V switcher ==
== Maker core rails and reverse-blocked header power outputs ==
== Direct internal USB, Pico utility GPIO, reset/boot, and SWD ==
== Protected user-facing maker GPIO header ==
LAYOUT-CRITICAL NOTES:
Place L901/C911/C912/C913/R907 exactly around U901 per Raspberry Pi RP2350 guidance; keep LX copper tiny.
Place R900/R901 at U901 USB pins and U906 in the short Mu path; route both pairs as 90-ohm differential over uninterrupted ground.
Keep Y900/R906/C918/C919 tight to XIN/XOUT. Keep QSPI traces short; place C902/C903 at U902.
No Pico module, Micro-USB receptacle, or internal USB cable is used. The integrated RP2350 is the USB device.
J901 is keyed/latching JST PUD 2.00mm and NOT Pi-HAT compatible. U910-U913 isolate and tolerate 5V at the connector; 5.5V-standoff U914-U921 provide connector-side ESD.
R932-R961 are 330R fault-limit resistors. Digital outputs are 3.3V only; use external I2C pull-ups >=4.7k and initially keep SPI/SWD <=10MHz.
The ADC reference remains internal. J901 ADC precision range is 0-3.0V; 5.5V tolerance is for accidental input only and must be validated, not treated as an ADC range.
U922/Q903 hold all 30 signals disconnected until MAKER_3V3_CORE is valid. Header power rails separately default OFF and are current-limited.
U906 defaults disconnected and connects only after physical INTERNAL_USB_VBUS is valid. The maker cannot wake S3; firmware reinitializes USB when MAKER_HOST_ACTIVE_N falls.
